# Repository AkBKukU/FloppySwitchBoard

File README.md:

# FloppySwitchBoard - Alpha

The Floppy Switch Board 
is designed to allow you to connect multiple (theoretically indefinite) floppy drives to
a single drive interface by letting you manually switch between them.

## How it works

Floppy drives using the Shugart drive interface have 4 ID wires that are used to identify the 
drives which are all connected to the same physical cable. When a floppy controller requests 
data from a floppy drive, the signals are sent to all connected drives. But only the drive
with the correct ID will respond. Each drive is configured, in some way, to have a unique ID.

The floppy Switch Board allows you to take one physical connector and connect two drives to 
it. It then intercepts and redirects the ID signal to one of the two drives using a switch.

## Compatibility

I just barely had these first batch of alpha prototype boards in and then unfortunately had 
to move. So my testing has been cut short in this area until I can get set back up to 
continue.

The board design as is should be compatible with at least IBM PC drive interfaces. The 
current revision of the board here switches not only the ID line but also the motor control
line which is needed for PCs. Unfortunately this is incompatible with pure shugart spec 
systems like the TRS-80s. I need to make a revision of the board that allows you to 
add/remove a jumper for switching the motor power line for PCs so it can be used with
more systems.

## Usage

Being a completely passive device the floppy switch board does not require drivers or 
software of any kind to work, but it can benefit from it which I will cover in a 
moment. The most simple setup would be connecting two drives to the system for use
with disk imaging software that directly controls the drive such as IMD or dskImage.
Drives connected to the board itself must use *non*-twisted cables. Additionally
because it switches the ID and motor lines it needs a DPDT switch for both signals
which I have not yet found a prewired solution for. So you will have to get a switch
and wire to put one together yourself.

For normal DOS use there is a more advanced configuration that can be done using 
`driver.sys`. There is [some](https://web.archive.org/web/20210412134354/http://info.wsisiz.edu.pl/~bse26236/batutil/help/DRIVER_S.HTM) documentaion on its features that allows you to manually
create new "virtual" floppy drives on an MS-DOS system. It is even smart enough to
know when you have multiple drives connected to the same ID to give you a moment to
confirm that the drive is ready. With `driver.sys` you can switch between both drives 
connected to the floppy switch board almost as if they were connected directly to the 
drive controller. It doesn't work with software that accesses drives directly though 
and doesn't work well with software that doesn't run on the command line. I don't have
time at the moment to write out a full guide on the usage of it and the one website I
found that detailed it will is gone and I forgot where it was. I will update this with
both a link and a full tutorial on it when I have the time.

The Floppy Switch Board can be used on a Windows system but it is not easy and to there
are issues. The `driver.sys` feature was removed in Windows DOS versions and I cannot
find an alternative feature to replace it. Since Windows uses the BIOS configuration 
for the floppy drives it will only ever have the drives you tell it exist there. Even 
if you connect two similar drives (such as two 1.44MB) Windows will not refresh the
ToC that lists the files on the disk in a way you expect which can make it difficult to
use. I need to do more testing to charactarize how this works and see if there is a 
solution. Imaging programs that directly access the hardware should still work though.

## Gotek?

Yes, this works with a Gotek! This is probably the easiest use for it because you will
most likely be using the Gotek to emulate the same type of drive you already have 
connected. By placing the floppy switch board in front an existing traditional floppy
drive you connect both it and the Gotek to a system and keep both usable(Keep in mind 
potential commpatibility issues because of the PC drive motor line though). 

## Roadmap
I will be updating this project and continuing development on it once I have settled in
to my new office. I have multiple things I need to correct on it before I am going to
call it done. I need to fix the following for the beta version:

 - Add jumper for motor select and possibly redo ID signalling entirely to support non-pcs
 - Changing mounting holes to match *something* on a floppy drive to make it easier to install

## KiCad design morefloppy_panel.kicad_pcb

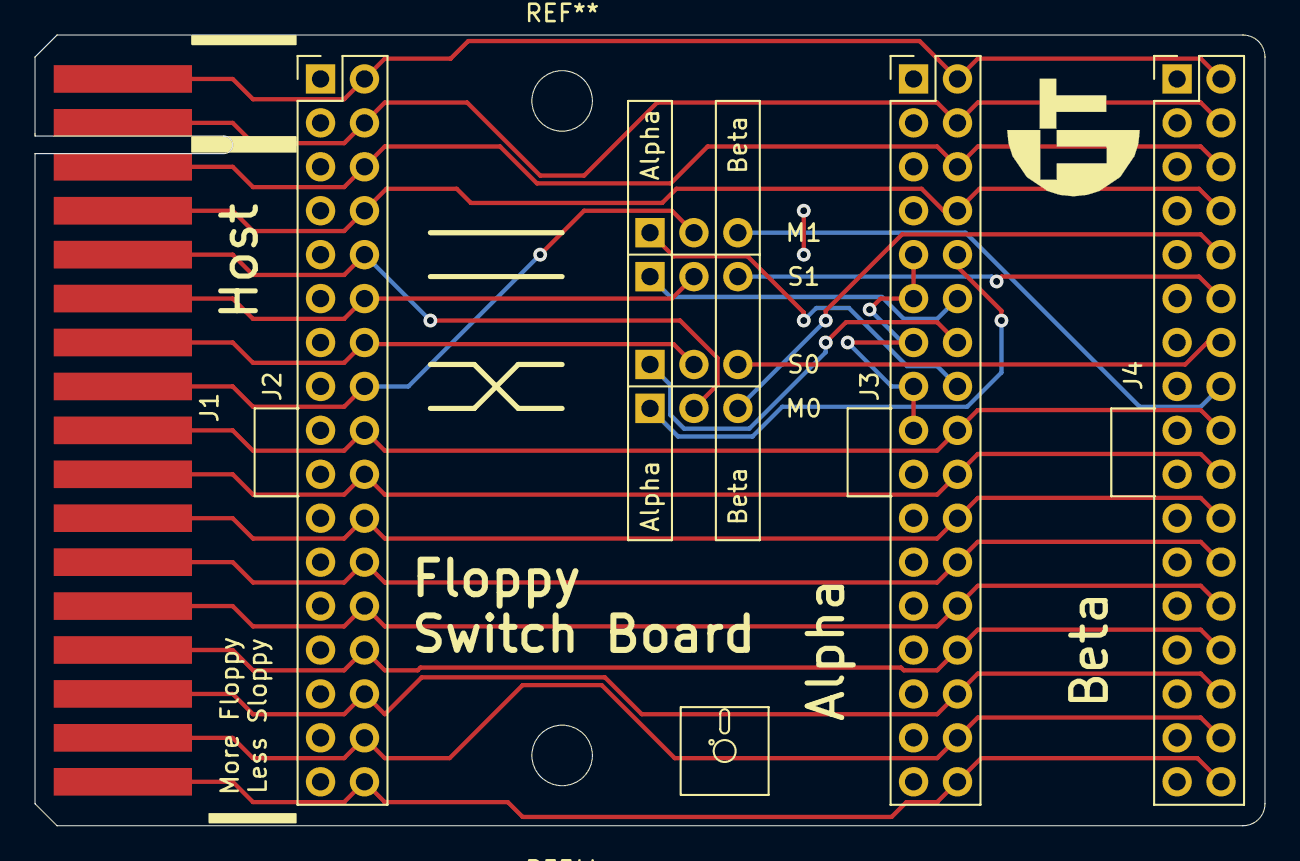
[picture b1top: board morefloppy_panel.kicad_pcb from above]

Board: 2 copper layers, 71.1 x 45.7 mm, 8 parts (0 on the bottom side), 26 nets.

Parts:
J1: PCFloppyHeader; FloppyCardEdge
J2, J3, J4: PCFloppyHeader; FloppyHeader
M0, M1: SW_SPDT; PinHeader_1x03_P2.54mm_Vertical
S0, S1: SW_SPDT; PinHeader_1x03_P2.54mm_Vertical

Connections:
DataRead: J1.30, J2.30, J3.30, J4.30
DataWrite: J1.22, J2.22, J3.22, J4.22
DesitySelect: J1.2, J2.2, J3.2, J4.2
DirectionSelect: J1.18, J2.18, J3.18, J4.18
DiskChange: J1.34, J2.34, J3.34, J4.34
DriveSelect0-In: J1.14, J2.14, S0.2
DriveSelect0-Out-A: J3.14, S0.1
DriveSelect0-Out-B: J4.14, S0.3
DriveSelect1-In: J1.12, J2.12, S1.2
DriveSelect1-Out-A: J3.12, S1.1
DriveSelect1-Out-B: J4.12, S1.3
GND: J1.1, J1.3, J1.5, J1.7, J1.9, J1.11, J1.13, J1.15, J1.17, J1.19, J1.21, J1.23, J1.25, J1.27, J1.29, J1.31, J1.33, J2.1, J2.3, J2.5, J2.7, J2.9, J2.11, J2.13, J2.15, J2.17, J2.19, J2.21, J2.23, J2.25, J2.27, J2.29, J2.31, J2.33, J3.1, J3.3, J3.5, J3.7, J3.9, J3.11, J3.13, J3.15, J3.17, J3.19, J3.21, J3.23, J3.25, J3.27, J3.29, J3.31, J3.33, J4.1, J4.3, J4.5, J4.7, J4.9, J4.11, J4.13, J4.15, J4.17, J4.19, J4.21, J4.23, J4.25, J4.27, J4.29, J4.31, J4.33
HeadSelect: J1.32, J2.32, J3.32, J4.32
Index: J1.8, J2.8, J3.8, J4.8
Motor0-In: J1.10, J2.10, M0.2
Motor0-Out-A: J3.10, M0.1
Motor0-Out-B: J4.10, M0.3
Motor1-In: J1.16, J2.16, M1.2
Motor1-Out-A: J3.16, M1.1
Motor1-Out-B: J4.16, M1.3
Reserved1: J1.4, J2.4, J3.4, J4.4
Reserved2: J1.6, J2.6, J3.6, J4.6
StepHead: J1.20, J2.20, J3.20, J4.20
Track00: J1.26, J2.26, J3.26, J4.26
WriteEnable: J1.24, J2.24, J3.24, J4.24
WriteProtect: J1.28, J2.28, J3.28, J4.28

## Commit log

2022-09-09 fix silk screen error and generate gerbers
